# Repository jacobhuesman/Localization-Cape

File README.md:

# bbb_localization_cape
BeagleBone Black Cape for Localization Project

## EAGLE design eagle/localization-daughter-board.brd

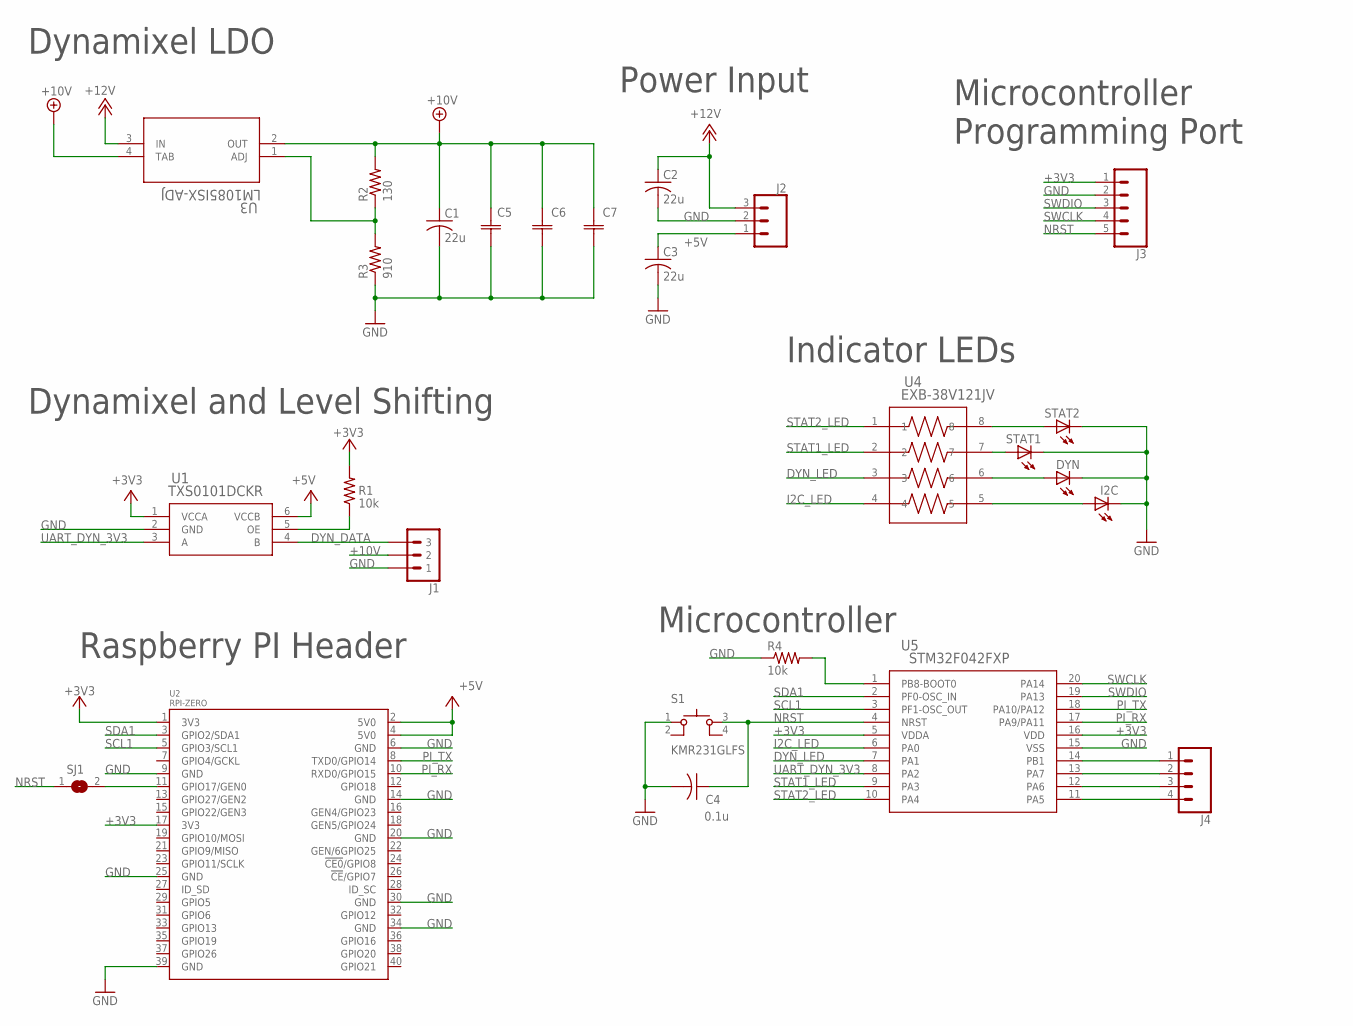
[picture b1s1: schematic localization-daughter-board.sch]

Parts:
C1: 22u; C1206
C2, C3: 22u; C0805
C4: 0.1u; C0805
C5, C6, C7: F931C107MCC; F93-C
DYN: LEDSML0603; SML0603
I2C: LEDSML0603; SML0603
J1: MOLEX-22-03-5035; MOLEX-22-05-7035
J2: CONN_03JST-PTH; JST-3-PTH
J3: CONN_05JST-VERT; JST-5-PTH-VERT
J4: CONN_041X04_NO_SILK; 1X04_NO_SILK
R1, R4: 10k; R0805
R2: 130; R0805
R3: 910; R0805
S1: KMR231GLFS
SJ1: SJ
STAT1, STAT2: LEDSML0603; SML0603
U1: TXS0101DCKR; DCK6
U2: RPI-ZERO; RASPBERRYPI_BASTELSTUBE_V13_RASPI_BOARD_B+_FULL
U3: LM1085ISX-ADJ; TS3B
U4: EXB-38V121JV; C_ARRAY_EXB38V
U5: STM32F042FXP; TSSOP20

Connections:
+3V3: J3.1, R1.2, U1.1 (VCCA), U2.1 (3V3), U2.17 (3V3), U5.5 (VDDA), U5.16 (VDD)
+5V: C3.1, J2.1, U1.6 (VCCB), U2.2 (5V0), U2.4 (5V0)
+10V: C1.1, C5.1, C6.1, C7.1, J1.P$2 (2), R2.2, U3.2 (OUT), U3.4 (TAB)
+12V: C2.1, J2.3, U3.3 (IN)
DYN_DATA: J1.P$3 (3), U1.4 (B)
DYN_LED: U4.3, U5.7 (PA1)
DYN_OE: R1.1, U1.5 (OE)
GND: C1.2, C2.2, C3.2, C4.2, C5.2, C6.2, C7.2, DYN.C, I2C.C, J1.P$1 (1), J2.2, J3.2, R3.1, R4.1, S1.1, STAT1.C, STAT2.C, U1.2 (GND), U2.6 (GND), U2.9 (GND), U2.14 (GND), U2.20 (GND), U2.25 (GND), U2.30 (GND), U2.34 (GND), U2.39 (GND), U5.15 (VSS)
I2C_LED: U4.4, U5.6 (PA0)
unnamed: R4.2, U5.1 (PB8-BOOT0)
unnamed: STAT1.A, U4.7
unnamed: R2.1, R3.2, U3.1 (ADJ)
unnamed: DYN.A, U4.6
unnamed: I2C.A, U4.5
unnamed: STAT2.A, U4.8
unnamed: J4.1, U5.14 (PB1)
unnamed: J4.2, U5.13 (PA7)
unnamed: J4.3, U5.12 (PA6)
unnamed: J4.4, U5.11 (PA5)
NRST: C4.1, J3.5, S1.3, SJ1.1, U5.4 (NRST)
PI_NRST: SJ1.2, U2.11 (GPIO17/GEN0)
PI_RX: U2.10 (RXD0/GPIO15), U5.17 (PA9/PA11)
PI_TX: U2.8 (TXD0/GPIO14), U5.18 (PA10/PA12)
SCL1: U2.5 (GPIO3/SCL1), U5.3 (PF1-OSC_OUT)
SDA1: U2.3 (GPIO2/SDA1), U5.2 (PF0-OSC_IN)
STAT1_LED: U4.2, U5.9 (PA3)
STAT2_LED: U4.1, U5.10 (PA4)
SWCLK: J3.4, U5.20 (PA14)
SWDIO: J3.3, U5.19 (PA13)
UART_DYN_3V3: U1.3 (A), U5.8 (PA2)

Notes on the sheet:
Dynamixel LDO
Dynamixel and Level Shifting
Microcontroller Programming Port
Raspberry PI Header
Microcontroller
Power Input
Indicator LEDs

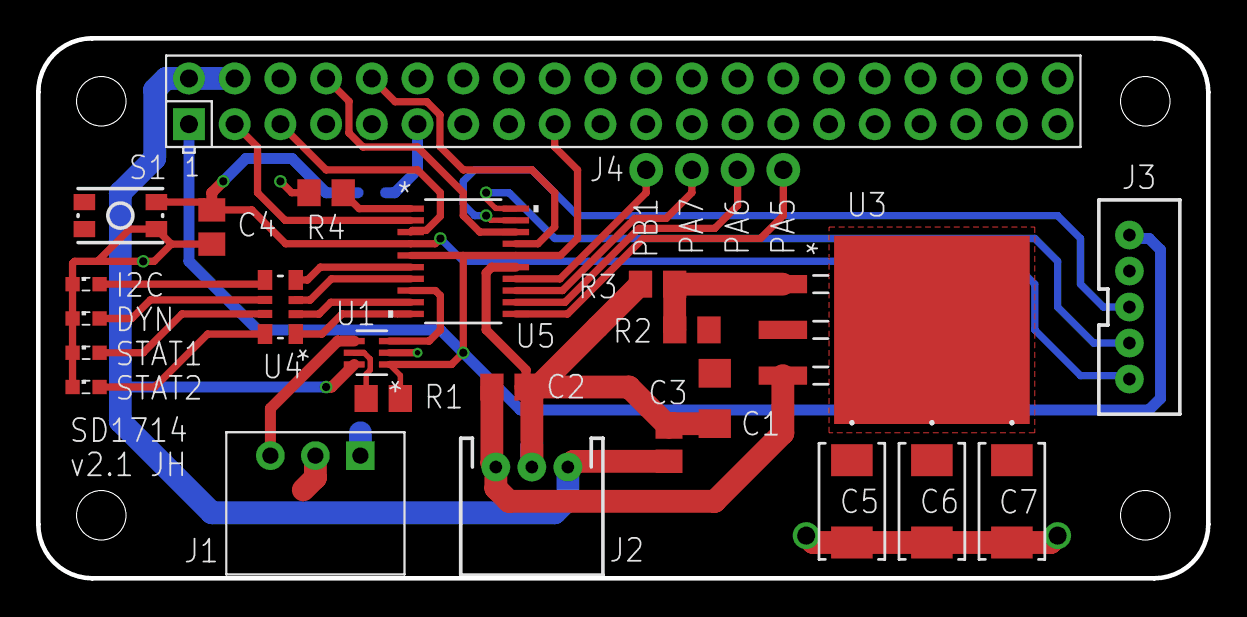
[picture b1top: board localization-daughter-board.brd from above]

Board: 2 copper layers, 65.0 x 30.0 mm, 26 parts (1 on the bottom side), 30 nets.

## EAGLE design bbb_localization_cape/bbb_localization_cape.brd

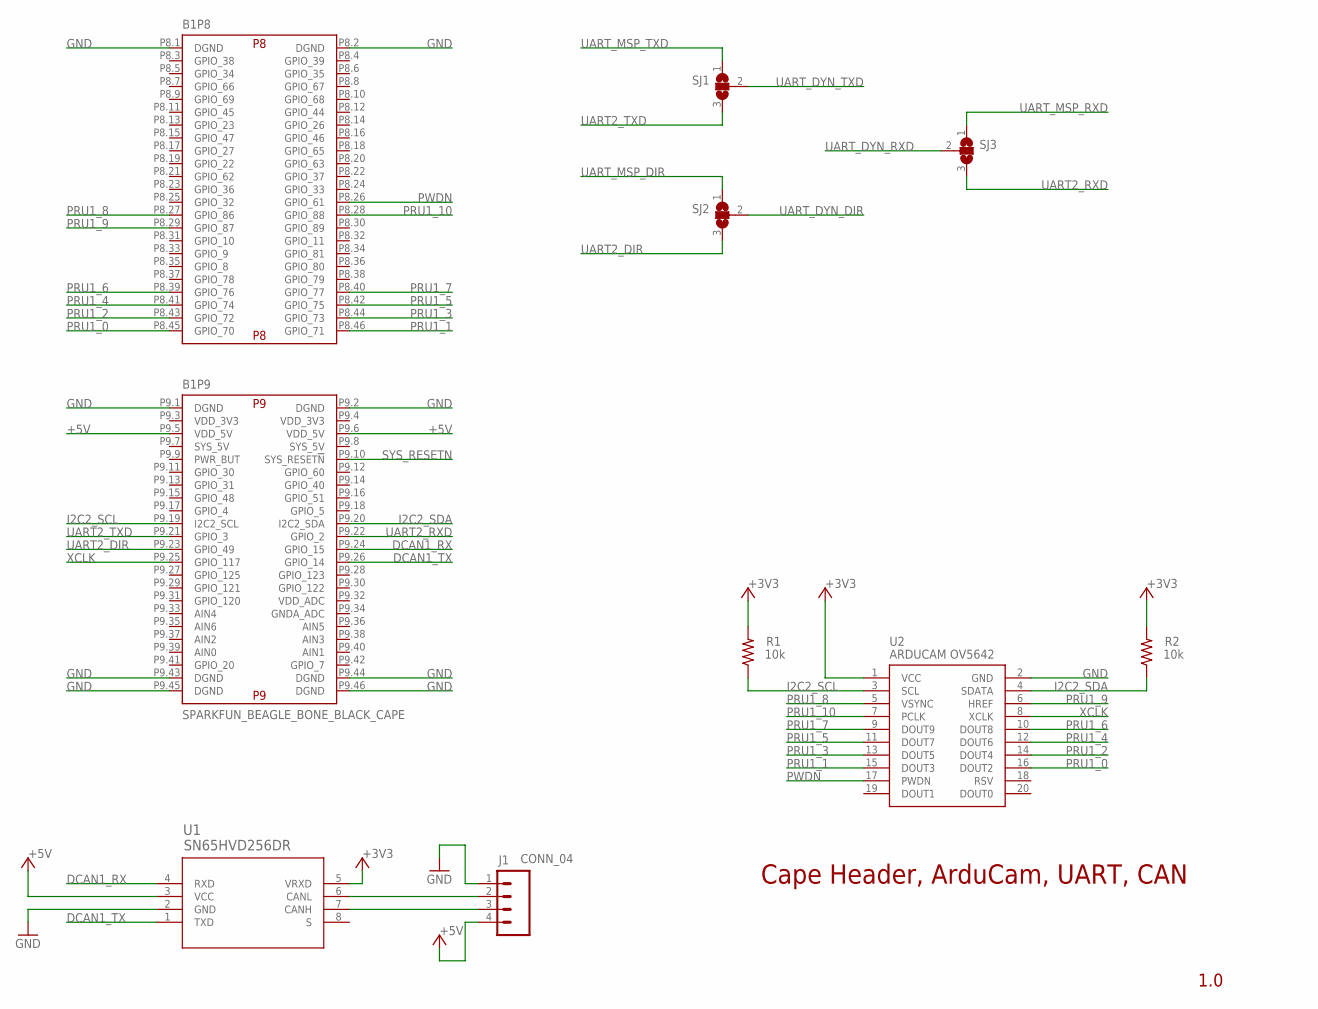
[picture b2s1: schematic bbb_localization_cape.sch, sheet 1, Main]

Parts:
B1: SPARKFUN_BEAGLE_BONE_BLACK_CAPE; BEAGLE_BONE_BLACK_CAPE
J1: CONN_04; JST-4-PTH-VERT; MANUFACTURER_PART_NUMBER B4B-PH-K-S(LF)(SN)
R1, R2: 10k; R0805; MANUFACTURER_PART_NUMBER RC0805JR-0710KL
SJ1, SJ2, SJ3: SJ2W; SJ_2
U1: SN65HVD256DR; D8
U2: ARDUCAMOV5642; ARDUCAM; MANUFACTURER_PART_NUMBER SSW-110-02-L-D

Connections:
+3V3: R1.2, R2.2, U1.5 (VRXD), U2.1 (VCC); also elsewhere on the board
+5V: B1.P9.5 (VDD_5V), B1.P9.6 (VDD_5V), J1.4, U1.3 (VCC); also elsewhere on the board
DCAN1_RX: B1.P9.24 (GPIO_15), U1.4 (RXD)
DCAN1_TX: B1.P9.26 (GPIO_14), U1.1 (TXD)
GND: B1.P8.1 (DGND), B1.P8.2 (DGND), B1.P9.1 (DGND), B1.P9.2 (DGND), B1.P9.43 (DGND), B1.P9.44 (DGND), B1.P9.45 (DGND), B1.P9.46 (DGND), J1.1, U1.2 (GND), U2.2 (GND); also elsewhere on the board
I2C2_SCL: B1.P9.19 (I2C2_SCL), R1.1, U2.3 (SCL); also elsewhere on the board
I2C2_SDA: B1.P9.20 (I2C2_SDA), R2.1, U2.4 (SDATA); also elsewhere on the board
unnamed: J1.2, U1.6 (CANL)
unnamed: J1.3, U1.7 (CANH)
PRU1_0: B1.P8.45 (GPIO_70), U2.16 (DOUT2)
PRU1_1: B1.P8.46 (GPIO_71), U2.15 (DOUT3)
PRU1_2: B1.P8.43 (GPIO_72), U2.14 (DOUT4)
PRU1_3: B1.P8.44 (GPIO_73), U2.13 (DOUT5)
PRU1_4: B1.P8.41 (GPIO_74), U2.12 (DOUT6)
PRU1_5: B1.P8.42 (GPIO_75), U2.11 (DOUT7)
PRU1_6: B1.P8.39 (GPIO_76), U2.10 (DOUT8)
PRU1_7: B1.P8.40 (GPIO_77), U2.9 (DOUT9)
PRU1_8: B1.P8.27 (GPIO_86), U2.5 (VSYNC)
PRU1_9: B1.P8.29 (GPIO_87), U2.6 (HREF)
PRU1_10: B1.P8.28 (GPIO_88), U2.7 (PCLK)
PWDN: B1.P8.26 (GPIO_61), U2.17 (PWDN)
SYS_RESETN: B1.P9.10 (SYS_RESET!N); also elsewhere on the board
UART2_DIR: B1.P9.23 (GPIO_49), SJ2.3
UART2_RXD: B1.P9.22 (GPIO_2), SJ3.3
UART2_TXD: B1.P9.21 (GPIO_3), SJ1.3
UART_DYN_DIR: SJ2.2; also elsewhere on the board
UART_DYN_RXD: SJ3.2; also elsewhere on the board
UART_DYN_TXD: SJ1.2; also elsewhere on the board
UART_MSP_DIR: SJ2.1; also elsewhere on the board
UART_MSP_RXD: SJ3.1; also elsewhere on the board
UART_MSP_TXD: SJ1.1; also elsewhere on the board
XCLK: B1.P9.25 (GPIO_117), U2.8 (XCLK)

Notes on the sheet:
Cape Header, ArduCam, UART, CAN
1.0

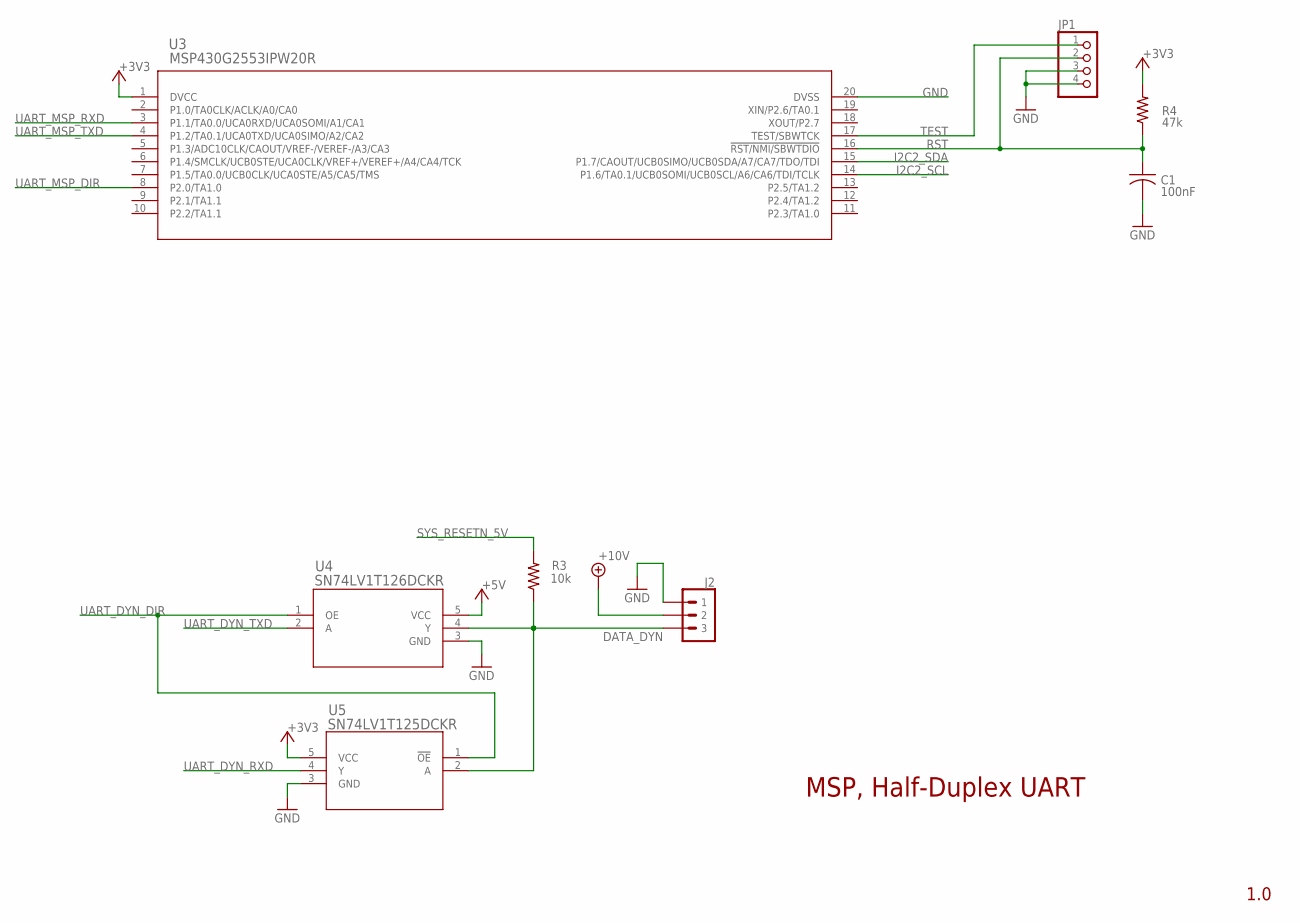
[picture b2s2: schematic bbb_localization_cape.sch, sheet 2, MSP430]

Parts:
C1: 100nF; C0805; MANUFACTURER_PART_NUMBER CL21B104KOANNNC
J2: MOLEX-22-03-5035; MANUFACTURER_PART_NUMBER 22-03-5035
JP1: PINHD-1X4; 1X04; MANUFACTURER_PART_NUMBER SSW-104-01-F-S
R3: 10k; R0805; MANUFACTURER_PART_NUMBER RC0805JR-0710KL
R4: 47k; R0805; MANUFACTURER_PART_NUMBER RMCF0805JT47K0
U3: MSP430G2553IPW20R; PW20
U4: SN74LV1T126DCKR; DCK5
U5: SN74LV1T125DCKR; DCK5

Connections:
+3V3: R4.2, U3.1 (DVCC), U5.5 (VCC); also elsewhere on the board
+5V: U4.5 (VCC); also elsewhere on the board
+10V: J2.P$2 (2); also elsewhere on the board
DATA_DYN: J2.P$3 (3), R3.1, U4.4 (Y), U5.2 (A)
GND: C1.2, J2.P$1 (1), JP1.3, JP1.4, U3.20 (DVSS), U4.3 (GND), U5.3 (GND); also elsewhere on the board
I2C2_SCL: U3.14 (P1.6/TA0.1/UCB0SOMI/UCB0SCL/A6/CA6/TDI/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); also elsewhere on the board
I2C2_SDA: U3.15 (P1.7/CAOUT/UCB0SIMO/UCB0SDA/A7/CA7/TDO/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); also elsewhere on the board
RST: C1.1, JP1.2, R4.1, U3.16 (!RST/NMI/SBWTDIO)
SYS_RESETN_5V: R3.2; also elsewhere on the board
TEST: JP1.1, U3.17 (TEST/SBWTCK)
UART_DYN_DIR: U4.1 (OE), U5.1 (!OE); also elsewhere on the board
UART_DYN_RXD: U5.4 (Y); also elsewhere on the board
UART_DYN_TXD: U4.2 (A); also elsewhere on the board
UART_MSP_DIR: U3.8 (P2.0/TA1.0); also elsewhere on the board
UART_MSP_RXD: U3.3 (P1.1/TA0.0/UCA0RXD/UCA0SOMI/A1/CA1); also elsewhere on the board
UART_MSP_TXD: U3.4 (P1.2/TA0.1/UCA0TXD/UCA0SIMO/A2/CA2); also elsewhere on the board

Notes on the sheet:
MSP, Half-Duplex UART
1.0

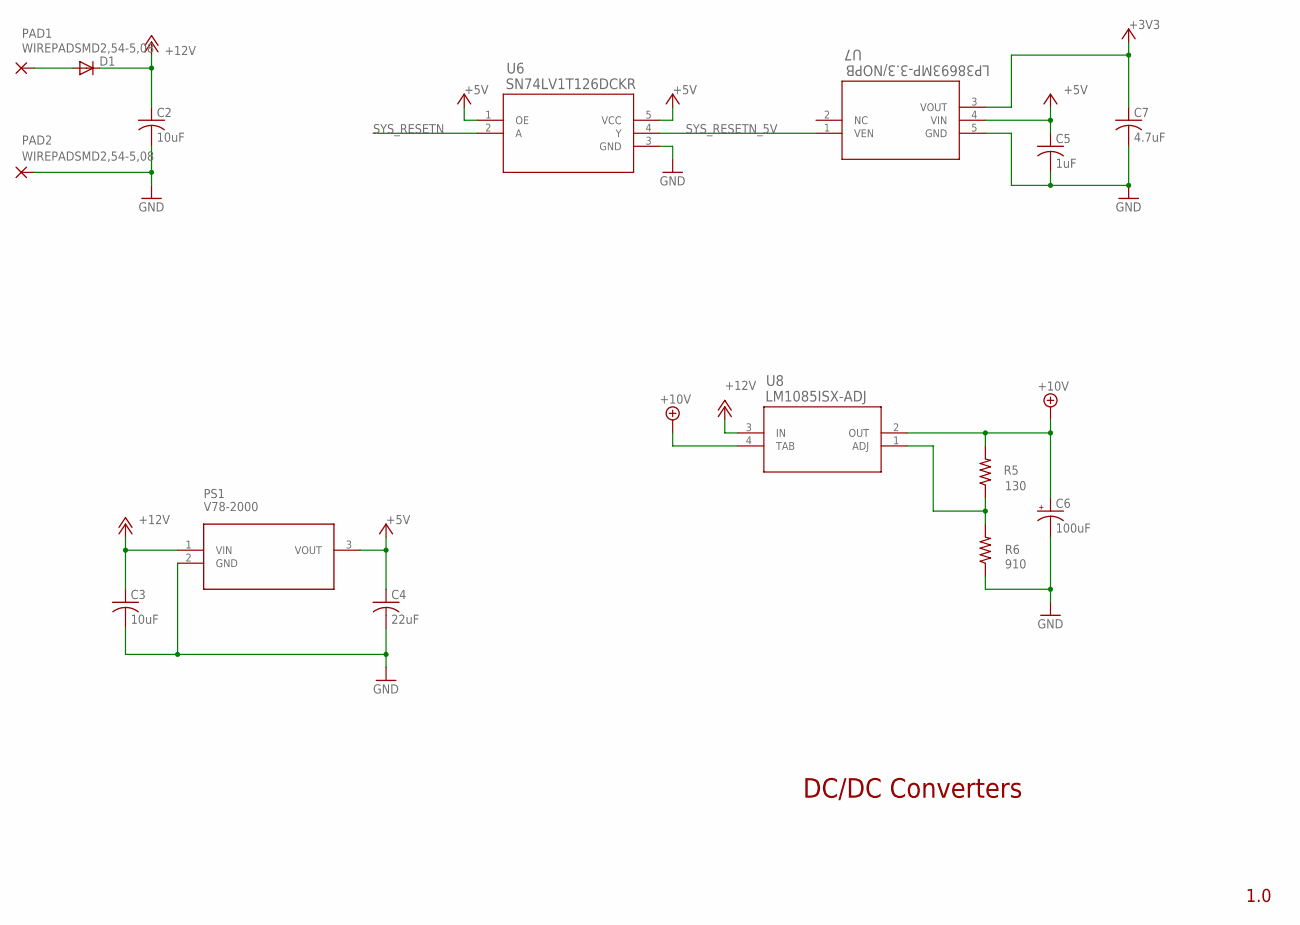
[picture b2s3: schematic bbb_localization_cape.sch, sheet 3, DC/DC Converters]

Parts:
C2, C3: 10uF; C0805; MANUFACTURER_PART_NUMBER GRM21BR61E106MA73L
C4: 22uF; C0805; MANUFACTURER_PART_NUMBER CL21A226MOCLRNC
C5: 1uF; C0805; MANUFACTURER_PART_NUMBER CL21B105KPFNNNE
C6: 100uF; PANASONIC_E; MANUFACTURER_PART_NUMBER C3216X5R1E476M160AC
C7: 4.7uF; C0805; MANUFACTURER_PART_NUMBER CL21A475KQFNNNG
D1: DIODE-DO-214AC; DO-214AC
PAD1, PAD2: WIREPADSMD2,54-5,08; SMD2,54-5,08
PS1: V78-2000; MANUFACTURER_PART_NUMBER V7805-2000R
R5: 130; R0805; MANUFACTURER_PART_NUMBER RC0805FR-07130RL
R6: 910; R0805; MANUFACTURER_PART_NUMBER RC0805FR-07910RL
U6: SN74LV1T126DCKR; DCK5
U7: LP38693MP-3.3/NOPB; MP05A; MANUFACTURER_PART_NUMBER LP38693MP-3.3/NOPB
U8: LM1085ISX-ADJ; TS3B; MANUFACTURER_PART_NUMBER LM1085ISX-ADJ/NOPB

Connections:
+3V3: C7.1, U7.3 (VOUT); also elsewhere on the board
+5V: C4.1, C5.1, PS1.3 (VOUT), U6.1 (OE), U6.5 (VCC), U7.4 (VIN); also elsewhere on the board
+10V: C6.+, R5.2, U8.2 (OUT), U8.4 (TAB); also elsewhere on the board
+12V: C2.1, C3.1, D1.C, PS1.1 (VIN), U8.3 (IN)
GND: C2.2, C3.2, C4.2, C5.2, C6.-, C7.2, PAD2.1, PS1.2 (GND), R6.1, U6.3 (GND), U7.5 (GND); also elsewhere on the board
unnamed: R5.1, R6.2, U8.1 (ADJ)
unnamed: D1.A, PAD1.1
SYS_RESETN: U6.2 (A); also elsewhere on the board
SYS_RESETN_5V: U6.4 (Y), U7.1 (VEN); also elsewhere on the board

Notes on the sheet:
DC/DC Converters
1.0

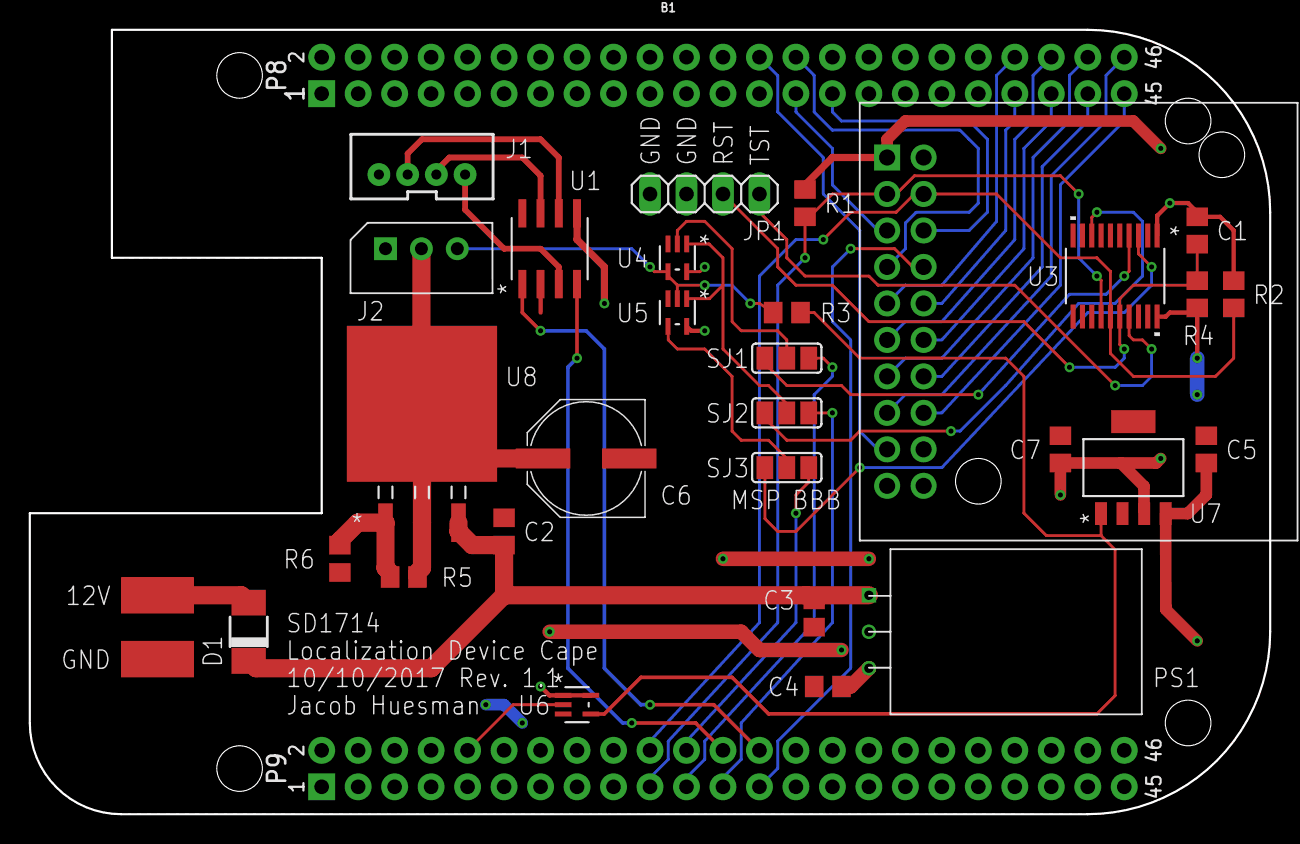
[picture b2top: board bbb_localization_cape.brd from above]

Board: 2 copper layers, 86.4 x 54.6 mm, 32 parts (0 on the bottom side), 40 nets.

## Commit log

2017-09-09 Started on cape
2017-09-16 Finished with DCDC converters and can transciever
2017-09-16 Started on arducam device
2017-09-19 Almost done wiring camera
2017-09-19 Decrusted the layout
2017-09-19 Almost done with camera signals
2017-09-20 Switched to ceramic capacitors
2017-09-20 Finished camera connections
2017-09-20 Added decoupling capacitors to each DC/DC converter input
2017-09-20 Deleted redundant libraries and started on molex package
2017-10-07 Started adding the microcontroller
2017-10-07 Added uart solder jumpers
2017-10-07 Added power to MSP430
2017-10-07 Consolidated libraries into bbb_cape_parts
2017-10-07 Changed library name
2017-10-07 Changed the name of the library again
2017-10-07 Cleaned up schematic and board
2017-10-07 Cleaning up schematic and board layout
2017-10-07 Added frames
2017-10-07 Laid out the board again
2017-10-07 Almost finished with component layout
2017-10-07 More or less finished with the schematic and layout
2017-10-07 Create ground plane
2017-10-07 Laid out power connections
2017-10-07 Finished board layout
2017-10-08 Fixed issues between board and schematic, had to ripup the board
2017-10-08 Cleaned up beaglebone_outline schematic symbol
2017-10-08 Went over the entire schematic
2017-10-08 Added components to deal with voltages during poweroff
2017-10-09 Consolidated powerdown level shifters from 2 to 1
2017-10-09 Added 10V and 5V lines
2017-10-09 Most of components placed
2017-10-09 Going to commit before I mess stuff up
2017-10-10 Laid out most of camera module traces
2017-10-10 Just checking in
2017-10-10 Done for the night
2017-10-10 Fixed the PTH mistakes
2017-10-10 Passing ERC, still need to go through DRC
2017-10-10 Finished routing signals, passing ERC and DRC
2017-10-10 Labeled everything
2017-10-10 Done, needs external review
2017-10-10 Updated schematic
2017-10-10 Added ground plane
2017-10-11 Added power planes
2017-10-11 Began adding 3D models of components
2017-10-12 Almost done adding 3D models
2017-10-12 Done
2017-10-13 Finished BOM
2017-10-24 Updated pdf and other things
2017-11-16 Changed board part from Adafruit to Sparkfun version
2017-11-16 Finished changing cape style
2017-11-16 Added reverse current protection and changed PWDN pin
2017-11-16 Changed XCLK
2017-11-16 Added dimension layer
2017-11-16 Fixed GND path
2017-11-16 Updated 3D models
2017-11-16 Started on buffer
2017-11-18 Started on v2.0
2017-11-18 Added latex .gitignore entries
2017-11-18 Put documents in an area that makes sense
2017-11-18 Removed pocket_beagle repo files
2017-11-18 Reconfigured document
2017-11-18 Added code view
2017-11-18 Moved documentation to the team repo
2017-12-11 Started on new board
2017-12-11 Just saving progress
2017-12-11 Finished initial schematic
2017-12-11 Fixed dynamixel connections
2017-12-11 Finished initial power layout
2017-12-11 Finished initial design
2017-12-11 Removed redundant pull-up resistor
2017-12-11 Finished board
2017-12-18 Updated schematic and BOM
2018-01-26 Added most of the new components
2018-01-26 Finished layout, need to do final check
2018-01-26 Fixed a few nasty traces and did ERC and DRC
2018-01-26 Added a few comments to the schematic
2018-01-26 Removed extra files and updated pdf
2018-01-26 Broke out the rest of the micro pins. Adjusted the font on connectors
2018-01-27 Fixed fonts again
2018-01-27 Current design
2018-01-27 Added library
2018-01-27 Added additional capacitors
2018-01-27 Finished

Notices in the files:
parts and their libraries:
SparkFun-Connectors: Licensing: Creative Commons ShareAlike 4.0 International - https://creativecommons.org/licenses/by-sa/4.0
